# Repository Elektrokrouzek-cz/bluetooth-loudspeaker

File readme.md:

# Bluetooth Loudspeaker
This is a construction of Bluetooth loudspeaker based on two finished modules.

PCB is 2-layer and was designed using KiCad 10. Fabrication output for JLCPCB is in 
gerber folder.

**Happy soldering!**

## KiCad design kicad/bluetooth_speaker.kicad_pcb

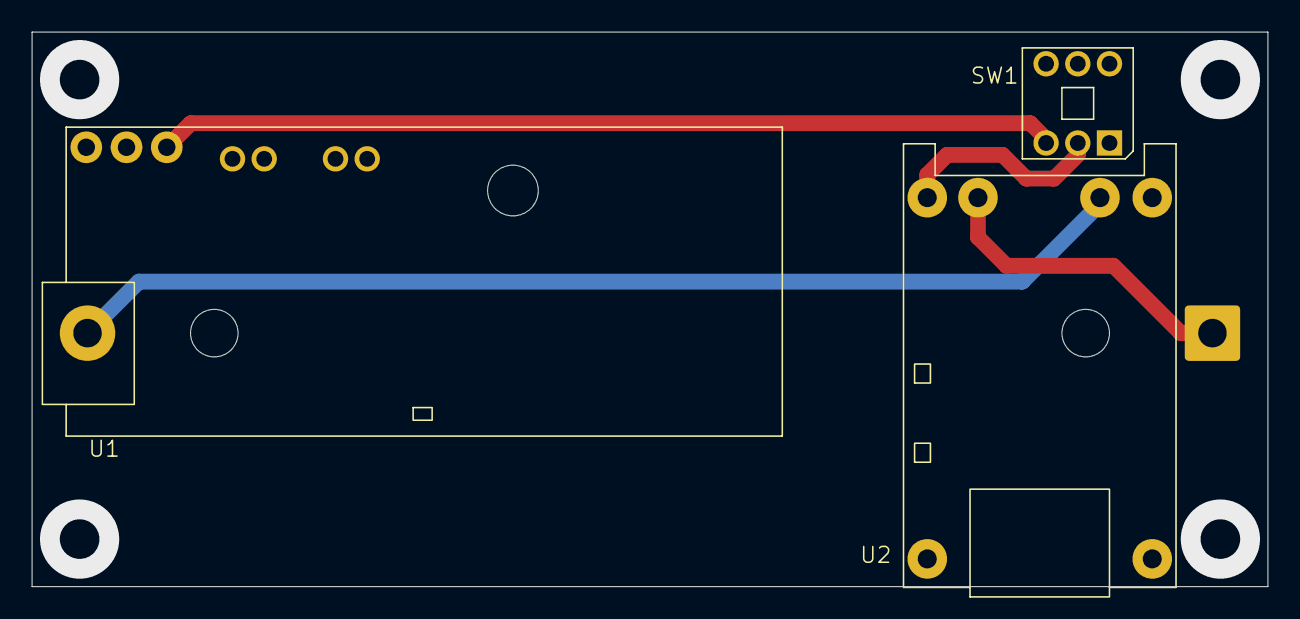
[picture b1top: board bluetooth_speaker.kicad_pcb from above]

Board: 2 copper layers, 78.0 x 35.0 mm, 4 parts (1 on the bottom side), 5 nets.

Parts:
BT1: 18650; BatHolder_18650
SW1: 7x7mm; SW_DPDT_7x7_Turbo
U1: Bluetooth_MH-M38
U2: Charger_TP4056

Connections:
GND: U1.1 (GND), U2.2 (OUT-)
unnamed: BT1.1 (+), U2.4 (BAT+)
unnamed: BT1.2 (-), U2.3 (BAT-)
unnamed: SW1.3 (C), U1.3 (VBAT)
unnamed: SW1.2 (B), U2.5 (OUT+)
